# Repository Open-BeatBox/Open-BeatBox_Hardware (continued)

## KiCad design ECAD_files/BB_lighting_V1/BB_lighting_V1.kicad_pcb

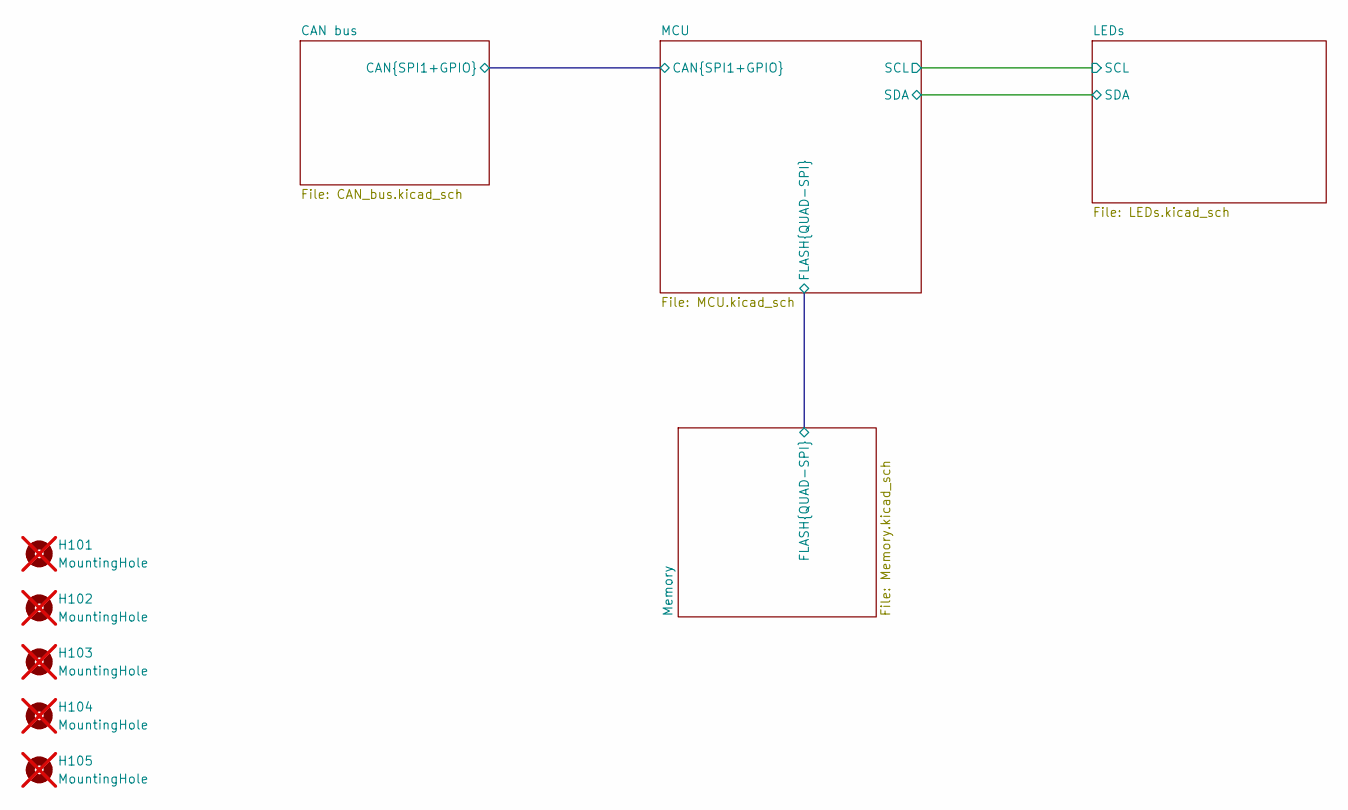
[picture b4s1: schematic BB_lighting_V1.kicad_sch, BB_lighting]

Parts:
H101, H102, H103, H104, H105: MountingHole; not fitted

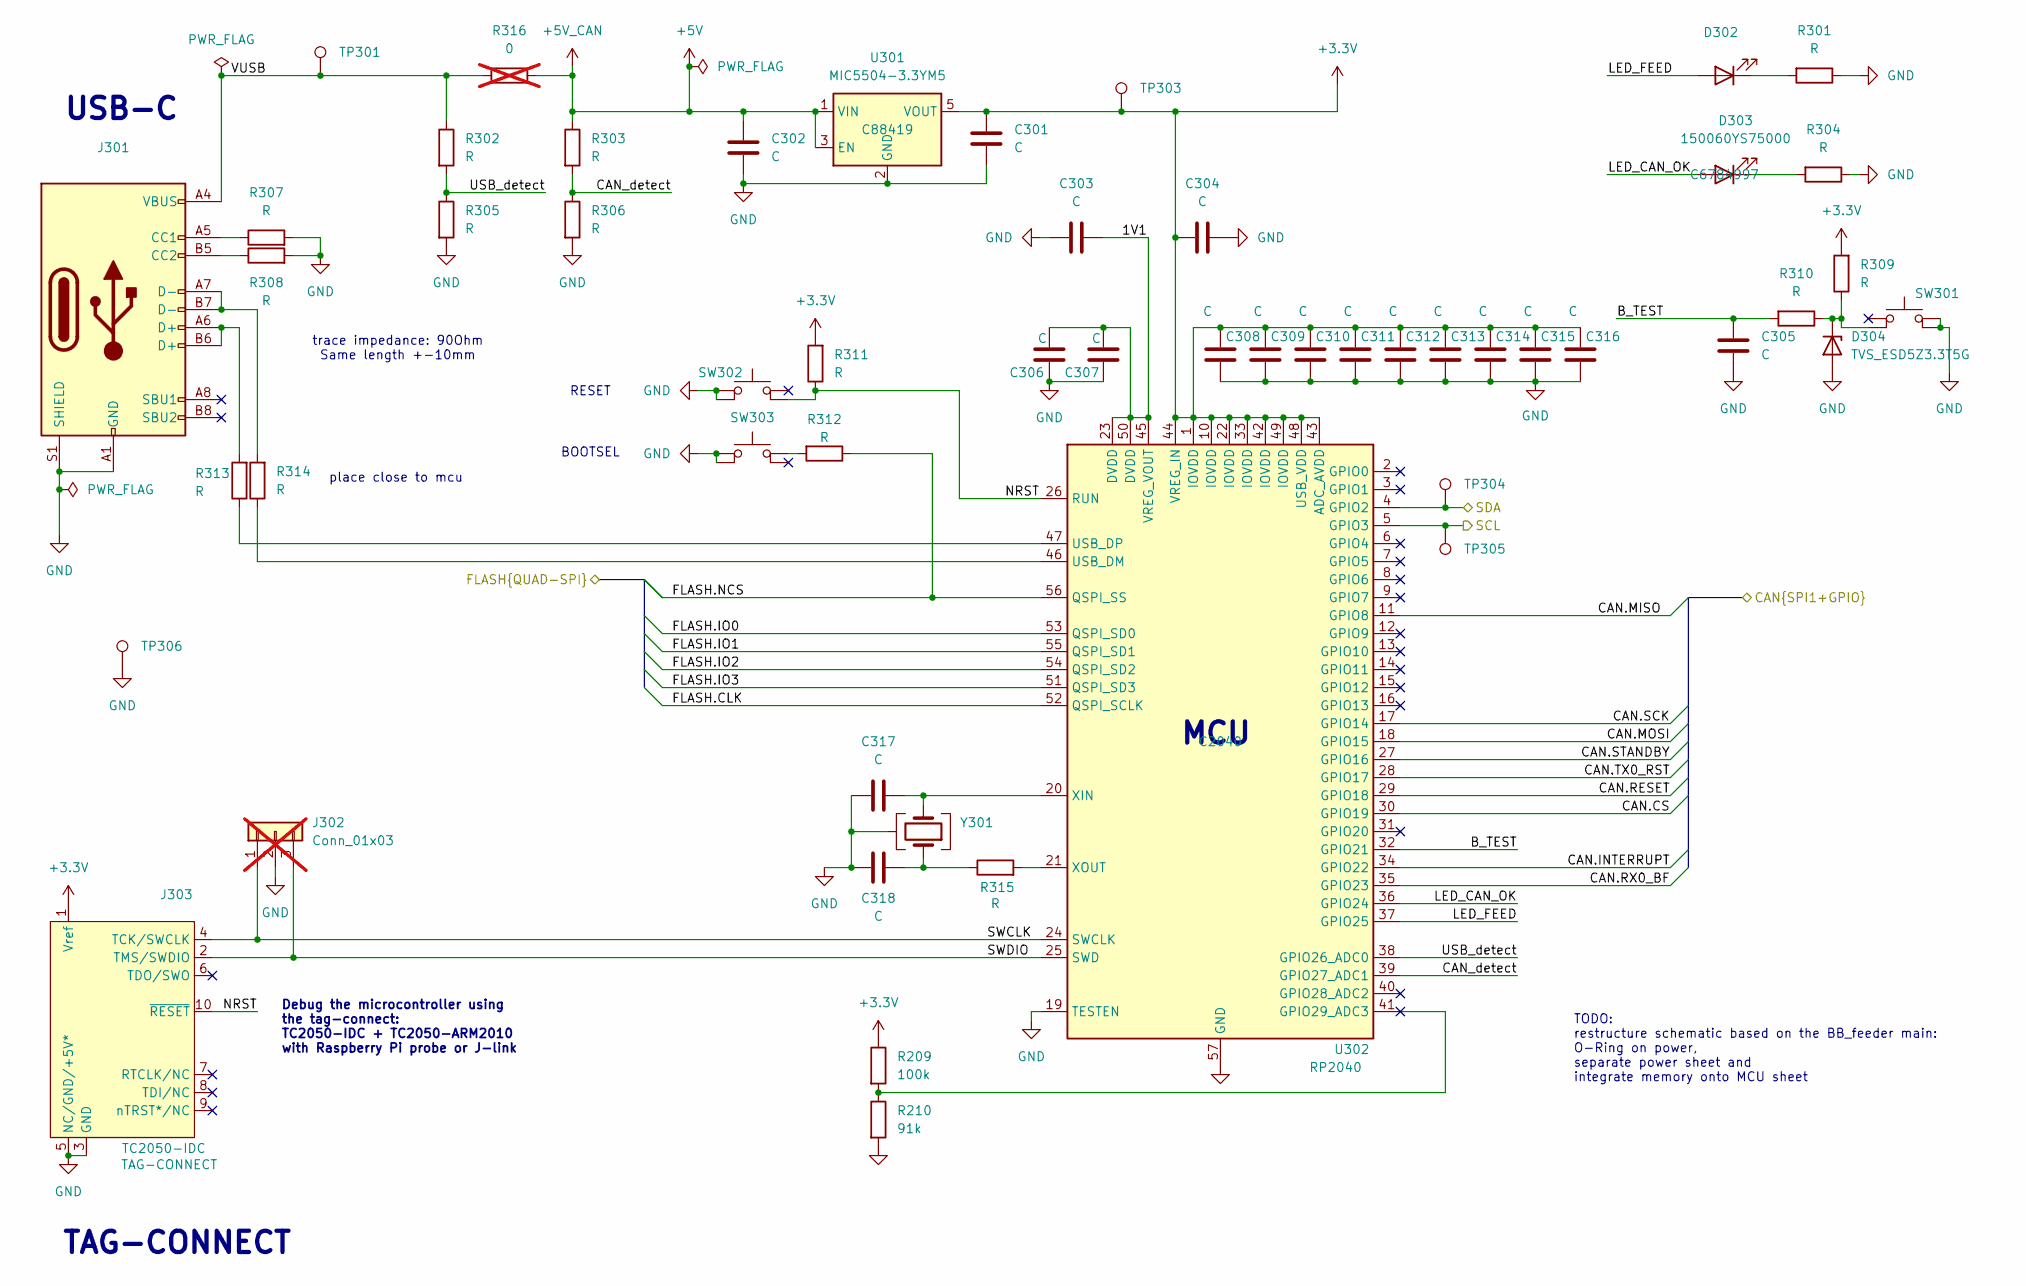
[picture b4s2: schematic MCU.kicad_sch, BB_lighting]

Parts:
C301, C302, C303, C304, C305, C306, C307, C308, C309, C310, C311, C312, C313, C314, C315, C316, C317, C318: C
D302: LED_150060GS75000; LED_0603_1608Metric; MPN 150060GS75000; JLCPCB Part C5252984
D303: LED_150060YS75000; LED_0603_1608Metric; MPN 150060YS75000; JLCPCB Part C6784997
D304: TVS_ESD5Z3.3T5G; D_SOD-523; MPN ESD5Z3.3T5G; JLCPCB Part C22440024
J301: Conn_USB-C_USB4105-GF-A; Conn_USB_C_Receptacle_GCT_USB4105-xx-A_16P_TopMnt_Horizontal; MPN USB4105-GF-A; JLCPCB Part C393939
J302: Conn_01x03; not fitted
J303: Conn_TagConnect_TC2050-IDC; Tag-Connect_TC2050-IDC-FP_2x05_P1.27mm_Vertical; MPN TC2050-IDC
R209: 100k; R_0603_1608Metric
R210: 91k; R_0603_1608Metric
R301, R302, R303, R304, R305, R306, R307, R308, R309, R310, R311, R312, R313, R314, R315: R
R316: 0; R_0603_1608Metric; not fitted
SW301, SW302, SW303: SW_TL3305AF160QG; SW_Push_TL3305; MPN TL3305AF160QG; JLCPCB Part C18078070
TP301, TP303, TP306: TestPoint; TestPoint_THTPad_D2.0mm_Drill1.0mm
TP304, TP305: TestPoint_SMD; TestPoint_Pad_D1.0mm
U301: MIC5504-3.3YM5; SOT-23-5; MPN MIC5504-3.3YM5; JLCPCB Part C88419
U302: RP2040; QFN-56-1EP_7x7mm_P0.4mm_EP3.2x3.2mm; MPN RP2040; JLCPCB Part C2040
Y301: Crystal_ABM8-272-T3; Crystal_SMD_Abracon_ABM8; MPN ABM8-272-T3; JLCPCB Part C20625731

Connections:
+3.3V: C301.1, C304.1, C308.1, C309.1, C310.1, C311.1, C312.1, C313.1, C314.1, C315.1, C316.1, J303.1 (Vref), R209.1, R309.2, R311.2, TP303.1 (1_1), U301.5 (VOUT), U302.1 (IOVDD), U302.10 (IOVDD), U302.22 (IOVDD), U302.33 (IOVDD), U302.42 (IOVDD), U302.43 (ADC_AVDD), U302.44 (VREG_IN), U302.48 (USB_VDD), U302.49 (IOVDD); also elsewhere on the board
+5V: C302.1, R303.1, R316.2, U301.1 (VIN), U301.3 (EN); also elsewhere on the board
/CAN bus/CAN.CS: U302.30 (GPIO19); also elsewhere on the board
/CAN bus/CAN.INTERRUPT: U302.34 (GPIO22); also elsewhere on the board
/CAN bus/CAN.MISO: U302.11 (GPIO8); also elsewhere on the board
/CAN bus/CAN.MOSI: U302.18 (GPIO15); also elsewhere on the board
/CAN bus/CAN.RESET: U302.29 (GPIO18); also elsewhere on the board
/CAN bus/CAN.RX0_BF: U302.35 (GPIO23); also elsewhere on the board
/CAN bus/CAN.SCK: U302.17 (GPIO14); also elsewhere on the board
/CAN bus/CAN.STANDBY: U302.27 (GPIO16); also elsewhere on the board
/CAN bus/CAN.TX0_RST: U302.28 (GPIO17); also elsewhere on the board
/LEDs/SCL: TP305.1 (1_1), U302.5 (GPIO3); also elsewhere on the board
/LEDs/SDA: TP304.1 (1_1), U302.4 (GPIO2); also elsewhere on the board
/MCU/1V1: C303.2, C306.2, C307.1, U302.23 (DVDD), U302.45 (VREG_VOUT), U302.50 (DVDD)
/MCU/B_TEST: C305.1, R310.2, U302.32 (GPIO21)
/MCU/CAN_detect: R303.2, R306.1, U302.39 (GPIO27_ADC1)
/MCU/FLASH.CLK: U302.52 (QSPI_SCLK); also elsewhere on the board
/MCU/FLASH.IO0: U302.53 (QSPI_SD0); also elsewhere on the board
/MCU/FLASH.IO1: U302.55 (QSPI_SD1); also elsewhere on the board
/MCU/FLASH.IO2: U302.54 (QSPI_SD2); also elsewhere on the board
/MCU/FLASH.IO3: U302.51 (QSPI_SD3); also elsewhere on the board
/MCU/FLASH.NCS: R312.1, U302.56 (QSPI_SS); also elsewhere on the board
/MCU/LED_CAN_OK: D303.2 (A), U302.36 (GPIO24)
/MCU/LED_FEED: D302.2 (A), U302.37 (GPIO25)
/MCU/NRST: J303.10 (~RESET), R311.1, SW302.2, U302.26 (RUN)
/MCU/SWCLK: J302.1, J303.4 (TCK/SWCLK), U302.24 (SWCLK)
/MCU/SWDIO: J302.3, J303.2 (TMS/SWDIO), U302.25 (SWD)
/MCU/USB_detect: R302.2, R305.1, U302.38 (GPIO26_ADC0)
/MCU/VUSB: J301.A4 (VBUS), J301.A9 (VBUS), J301.B4 (VBUS), J301.B9 (VBUS), R302.1, R316.1, TP301.1 (1_1)
GND: C301.2, C302.2, C303.1, C304.2, C305.2, C306.1, C307.2, C308.2, C309.2, C310.2, C311.2, C312.2, C313.2, C314.2, C315.2, C316.2, C317.1, C318.1, D304.2 (A), J301.A1 (GND), J301.A12 (GND), J301.B1 (GND), J301.B12 (GND), J301.S1 (SHIELD), J302.2, J303.3 (GND), J303.5 (NC/GND/+5V*), R210.2, R301.1, R304.1, R305.2, R306.2, R307.2, R308.2, SW301.1, SW301.2, SW302.3, SW302.4, SW303.1, SW303.2, TP306.1 (1_1), U301.2 (GND), U302.19 (TESTEN), U302.57 (GND), Y301.2, Y301.4; also elsewhere on the board
unnamed: C318.2, R315.1, Y301.1
unnamed: D302.1 (K), R301.2
unnamed: D303.1 (K), R304.2
unnamed: D304.1 (K), R309.1, R310.1, SW301.4
unnamed: J301.A5 (CC1), R307.1
unnamed: J301.B5 (CC2), R308.1
unnamed: J301.A6 (D+), J301.B6 (D+), R313.2
unnamed: J301.A7 (D-), J301.B7 (D-), R314.2
unnamed: R312.2, SW303.3
unnamed: R314.1, U302.46 (USB_DM)
unnamed: R313.1, U302.47 (USB_DP)
unnamed: C317.2, U302.20 (XIN), Y301.3
unnamed: R315.2, U302.21 (XOUT)

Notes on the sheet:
trace impedance: 90Ohm Same length +-10mm
TODO: restructure schematic based on the BB_feeder main: O-Ring on power, separate power sheet and integrate memory onto MCU sheet
TAG-CONNECT
MCU
place close to mcu
BOOTSEL
Debug the microcontroller using the tag-connect: TC2050-IDC + TC2050-ARM2010 with Raspberry Pi probe or J-link
RESET
USB-C

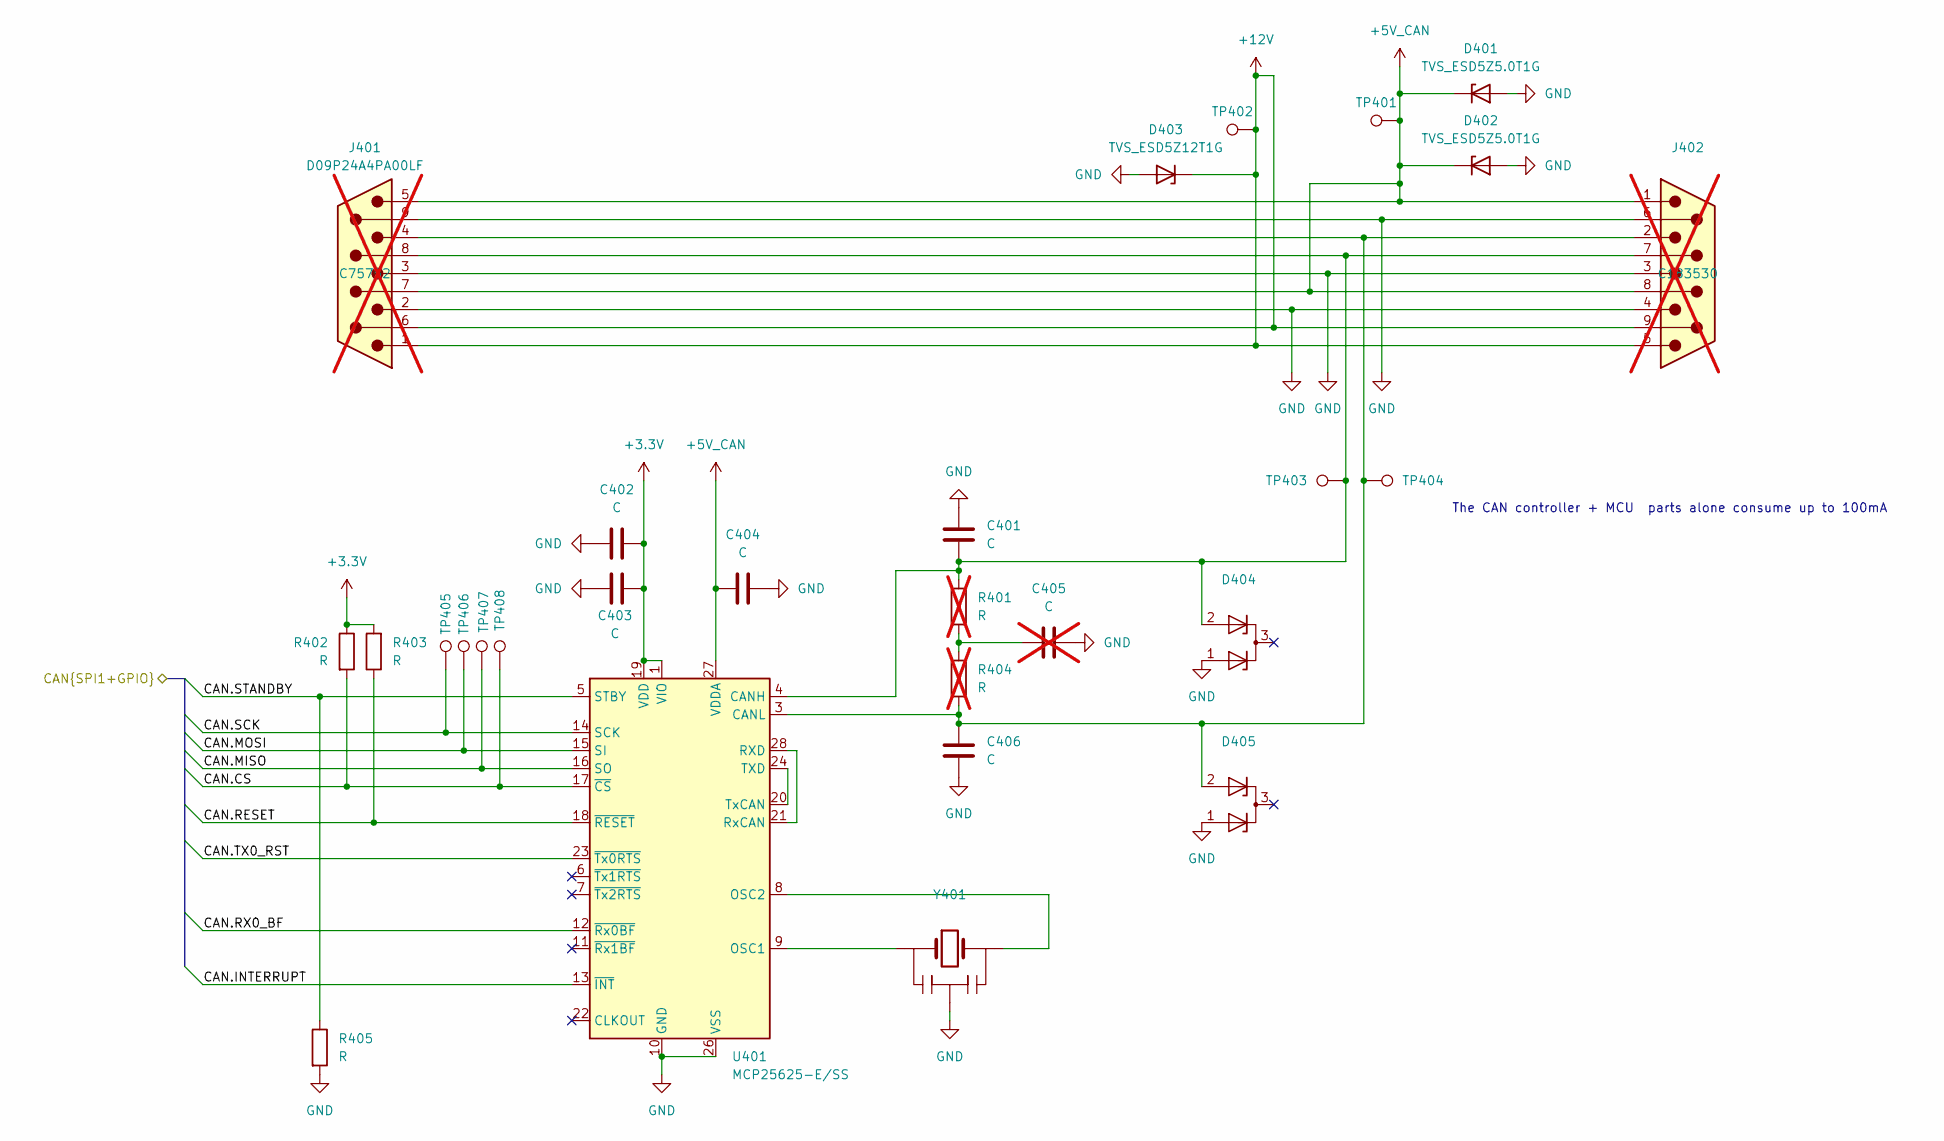
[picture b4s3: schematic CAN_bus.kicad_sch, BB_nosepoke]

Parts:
C401, C402, C403, C404, C406: C
C405: C; not fitted
D401, D402: TVS_ESD5Z5.0T1G; D_SOD-523; MPN ESD5Z5.0T1G; JLCPCB Part C343989
D403: TVS_ESD5Z12T1G; D_SOD-523; MPN ESD5Z12T1G
D404, D405: MMBZ27VCLT1G; SOT-23; MPN MMBZ27VCLT1G; JLCPCB Part C128609
J401: Conn-DB9_D09P24A4PA00LF; Conn_DB9_D09P24A4PA00LF; MPN D09P24A4PA00LF; JLCPCB Part C75752; not fitted
J402: Conn-DB9_D09S24A4PA00LF; Conn_DB9_D09S24A4PA00LF; MPN D09S24A4PA00LF; JLCPCB Part C183530; not fitted
R401, R404: R; not fitted
R402, R403, R405: R
TP401, TP402: TestPoint; TestPoint_THTPad_D2.0mm_Drill1.0mm
TP403, TP404, TP405, TP406, TP407, TP408: TestPoint_SMD; TestPoint_Pad_D1.0mm
U401: MCP25625-E/SS; SSOP-28_5.3x10.2mm_P0.65mm; MPN MCP25625-E/SS; JLCPCB Part C184944
Y401: CSTNE16M0VH3L000R0; Resonator_SMD_Murata_CSTxExxV-3Pin_3.0x1.1mm; MPN CSTNE16M0VH3L000R0; JLCPCB Part C1870467

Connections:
+3.3V: C402.2, C403.2, R402.1, R403.2, U401.1 (VIO), U401.19 (VDD); also elsewhere on the board
+5V: C404.1, D401.1 (K), D402.1 (K), J401.5, J401.7, J402.1, J402.8, TP401.1 (1_1), U401.27 (VDDA); also elsewhere on the board
+12V: D403.1 (K), J401.1, J401.6, J402.5, J402.9, TP402.1 (1_1); also elsewhere on the board
/CAN bus/CAN.CS: R402.2, TP408.1 (1_1), U401.17 (~CS); also elsewhere on the board
/CAN bus/CAN.INTERRUPT: U401.13 (~INT); also elsewhere on the board
/CAN bus/CAN.MISO: TP407.1 (1_1), U401.16 (SO); also elsewhere on the board
/CAN bus/CAN.MOSI: TP406.1 (1_1), U401.15 (SI); also elsewhere on the board
/CAN bus/CAN.RESET: R403.1, U401.18 (~RESET); also elsewhere on the board
/CAN bus/CAN.RX0_BF: U401.12 (~Rx0BF); also elsewhere on the board
/CAN bus/CAN.SCK: TP405.1 (1_1), U401.14 (SCK); also elsewhere on the board
/CAN bus/CAN.STANDBY: R405.1, U401.5 (STBY); also elsewhere on the board
/CAN bus/CAN.TX0_RST: U401.23 (~Tx0RTS); also elsewhere on the board
GND: C401.1, C402.1, C403.1, C404.2, C405.2, C406.2, D401.2 (A), D402.2 (A), D403.2 (A), D404.1 (K), D405.1 (K), J401.2, J401.3, J401.9, J402.3, J402.4, J402.6, R405.2, U401.10 (GND), U401.26 (VSS), Y401.2 (GND); also elsewhere on the board
unnamed: C405.1, R401.1, R404.2
unnamed: C401.2, D404.2 (K), J401.8, J402.7, R401.2, TP403.1 (1_1), U401.4 (CANH)
unnamed: C406.1, D405.2 (K), J401.4, J402.2, R404.1, TP404.1 (1_1), U401.3 (CANL)
unnamed: U401.9 (OSC1), Y401.1 (Input)
unnamed: U401.8 (OSC2), Y401.3 (Output)
unnamed: U401.21 (RxCAN), U401.28 (RXD)
unnamed: U401.20 (TxCAN), U401.24 (TXD)

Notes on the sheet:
The CAN controller + MCU parts alone consume up to 100mA

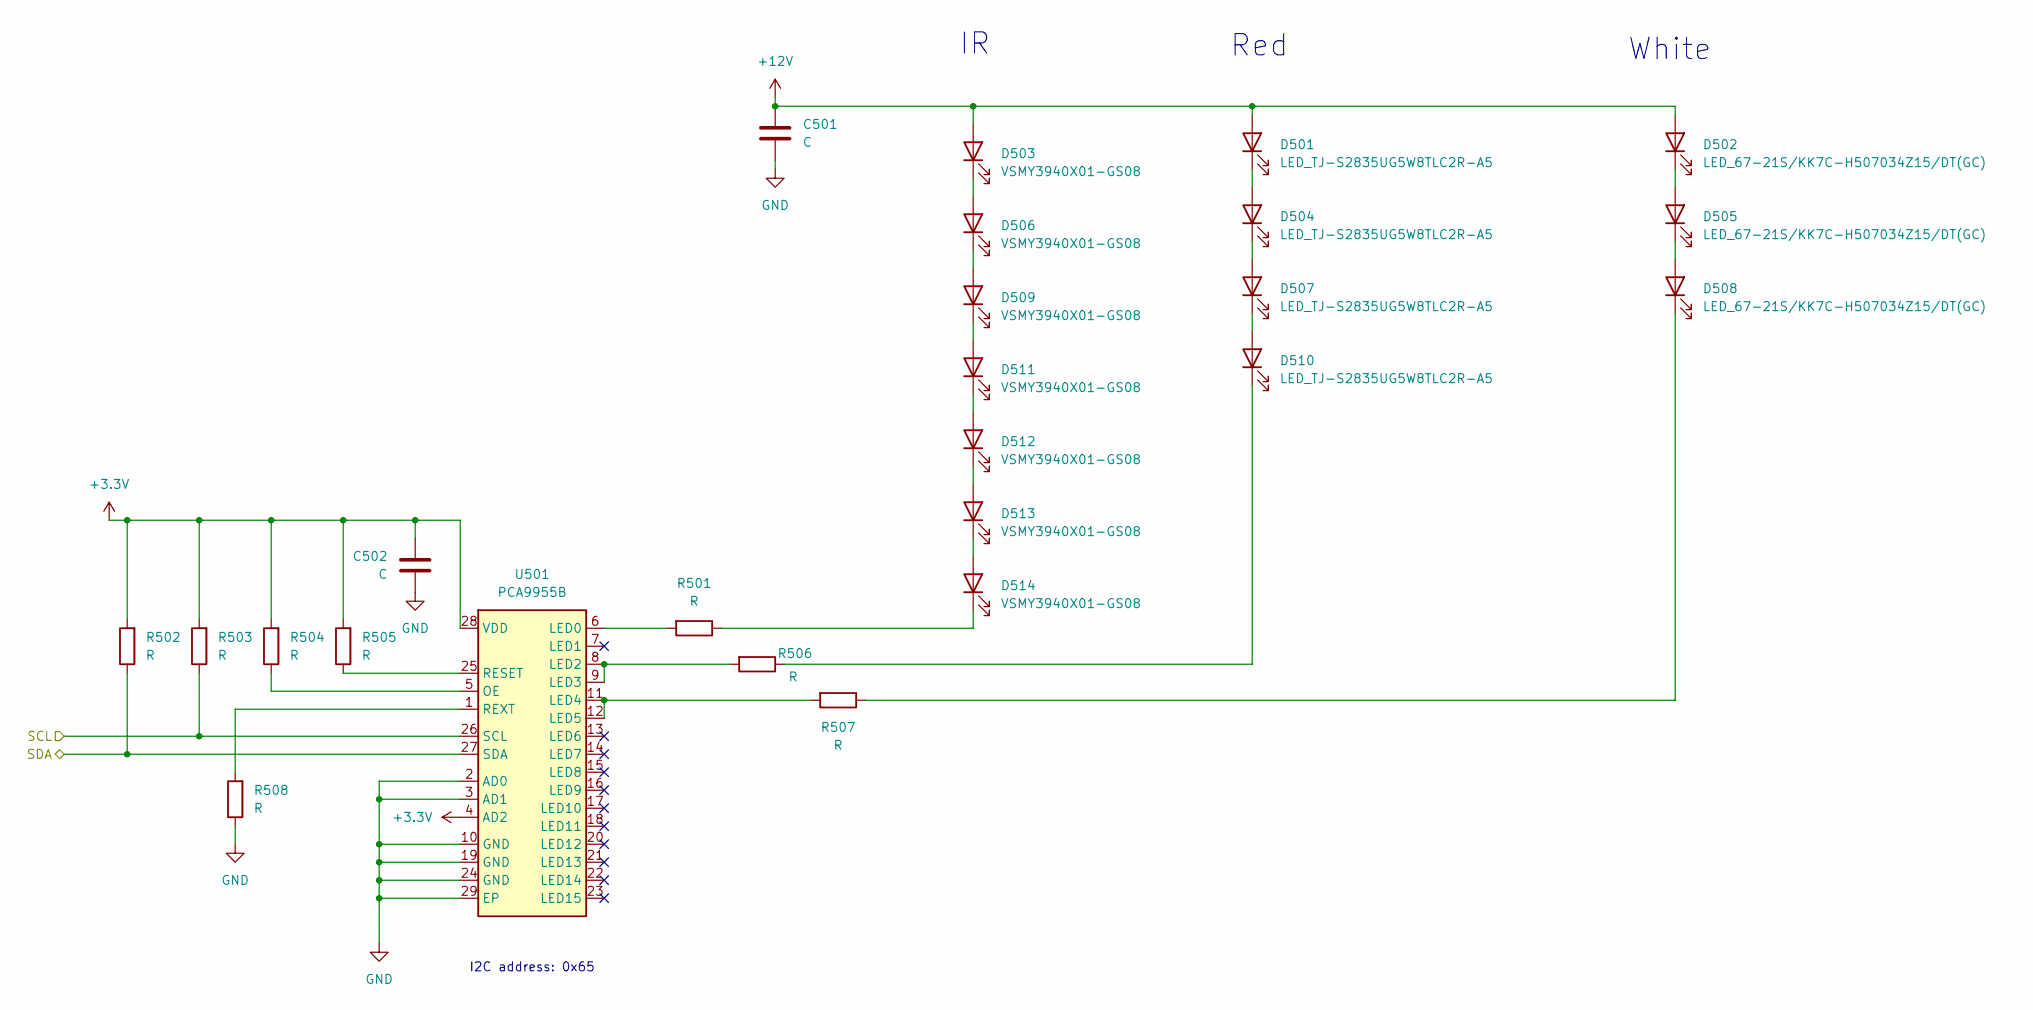
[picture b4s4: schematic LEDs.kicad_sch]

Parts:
C501, C502: C
D501, D504, D507, D510: LED_TJ-S2835UG5W8TLC2R-A5; LED_PLCC_2835_TOGIALED; MPN TJ-S2835UG5W8TLC2R-A5; JLCPCB Part C440450
D502, D505, D508: LED_67-21S/KK7C-H507034Z15/DT(GC); LED_PLCC_2835_Everlight; MPN 67-21S/KK7C-H507034Z15/DT(GC); JLCPCB Part C475394
D503, D506, D509, D511, D512, D513, D514: VSMY3940X01-GS08; LED_Vishay_PLCC-2; MPN VSMY3940X01-GS08; JLCPCB Part C962573
R501, R502, R503, R504, R505, R506, R507, R508: R
U501: PCA9955B; NXP_HTSSOP-28-1EP_4.4x9.7mm_P0.65mm_EP2.2x3.4mm; MPN PCA9955BTW/Q900J; JLCPCB Part C2678554

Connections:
+3.3V: C502.1, R502.2, R503.2, R504.2, R505.2, U501.4 (AD2), U501.28 (VDD); also elsewhere on the board
+12V: C501.1, D501.2 (A), D502.2 (A), D503.2 (A); also elsewhere on the board
/LEDs/SCL: R503.1, U501.26 (SCL); also elsewhere on the board
/LEDs/SDA: R502.1, U501.27 (SDA); also elsewhere on the board
GND: C501.2, C502.2, R508.1, U501.2 (AD0), U501.3 (AD1), U501.10 (GND), U501.19 (GND), U501.24 (GND), U501.29 (EP); also elsewhere on the board
unnamed: D501.1 (K), D504.2 (A)
unnamed: D502.1 (K), D505.2 (A)
unnamed: D503.1 (K), D506.2 (A)
unnamed: D504.1 (K), D507.2 (A)
unnamed: D505.1 (K), D508.2 (A)
unnamed: D506.1 (K), D509.2 (A)
unnamed: D507.1 (K), D510.2 (A)
unnamed: D508.1 (K), R507.1
unnamed: D509.1 (K), D511.2 (A)
unnamed: D510.1 (K), R506.1
unnamed: D511.1 (K), D512.2 (A)
unnamed: D512.1 (K), D513.2 (A)
unnamed: D513.1 (K), D514.2 (A)
unnamed: D514.1 (K), R501.1
unnamed: R501.2, U501.6 (LED0)
unnamed: R506.2, U501.8 (LED2), U501.9 (LED3)
unnamed: R507.2, U501.11 (LED4), U501.12 (LED5)
unnamed: R504.1, U501.5 (OE)
unnamed: R505.1, U501.25 (RESET)
unnamed: R508.2, U501.1 (REXT)

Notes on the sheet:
Red
I2C address: 0x65
White

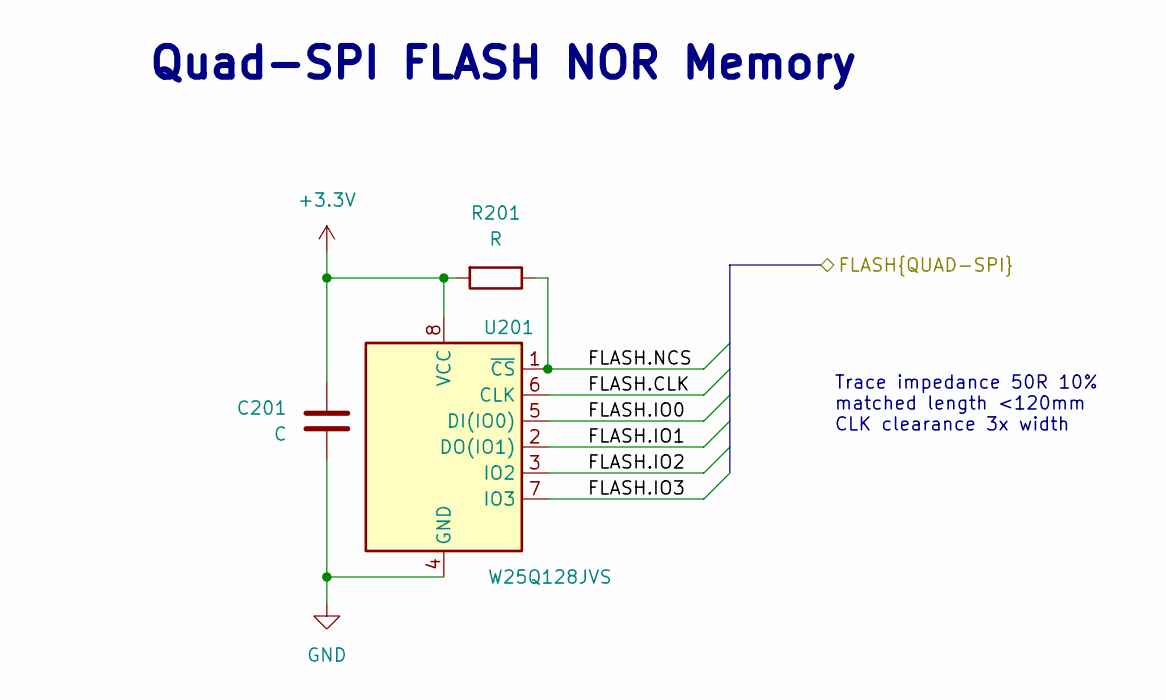
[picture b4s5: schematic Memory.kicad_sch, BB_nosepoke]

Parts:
C201: C
R201: R
U201: W25Q128JVS; SOIC-8_W25Q128JV; MPN W25Q128JVS; JLCPCB Part C97521

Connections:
+3.3V: C201.2, R201.2, U201.8 (VCC); also elsewhere on the board
/MCU/FLASH.CLK: U201.6 (CLK); also elsewhere on the board
/MCU/FLASH.IO0: U201.5 (DI(IO0)); also elsewhere on the board
/MCU/FLASH.IO1: U201.2 (DO(IO1)); also elsewhere on the board
/MCU/FLASH.IO2: U201.3 (IO2); also elsewhere on the board
/MCU/FLASH.IO3: U201.7 (IO3); also elsewhere on the board
/MCU/FLASH.NCS: R201.1, U201.1 (~CS); also elsewhere on the board
GND: C201.1, U201.4 (GND); also elsewhere on the board

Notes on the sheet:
Trace impedance 50R 10% matched length <120mm CLK clearance 3x width
Quad-SPI FLASH NOR Memory

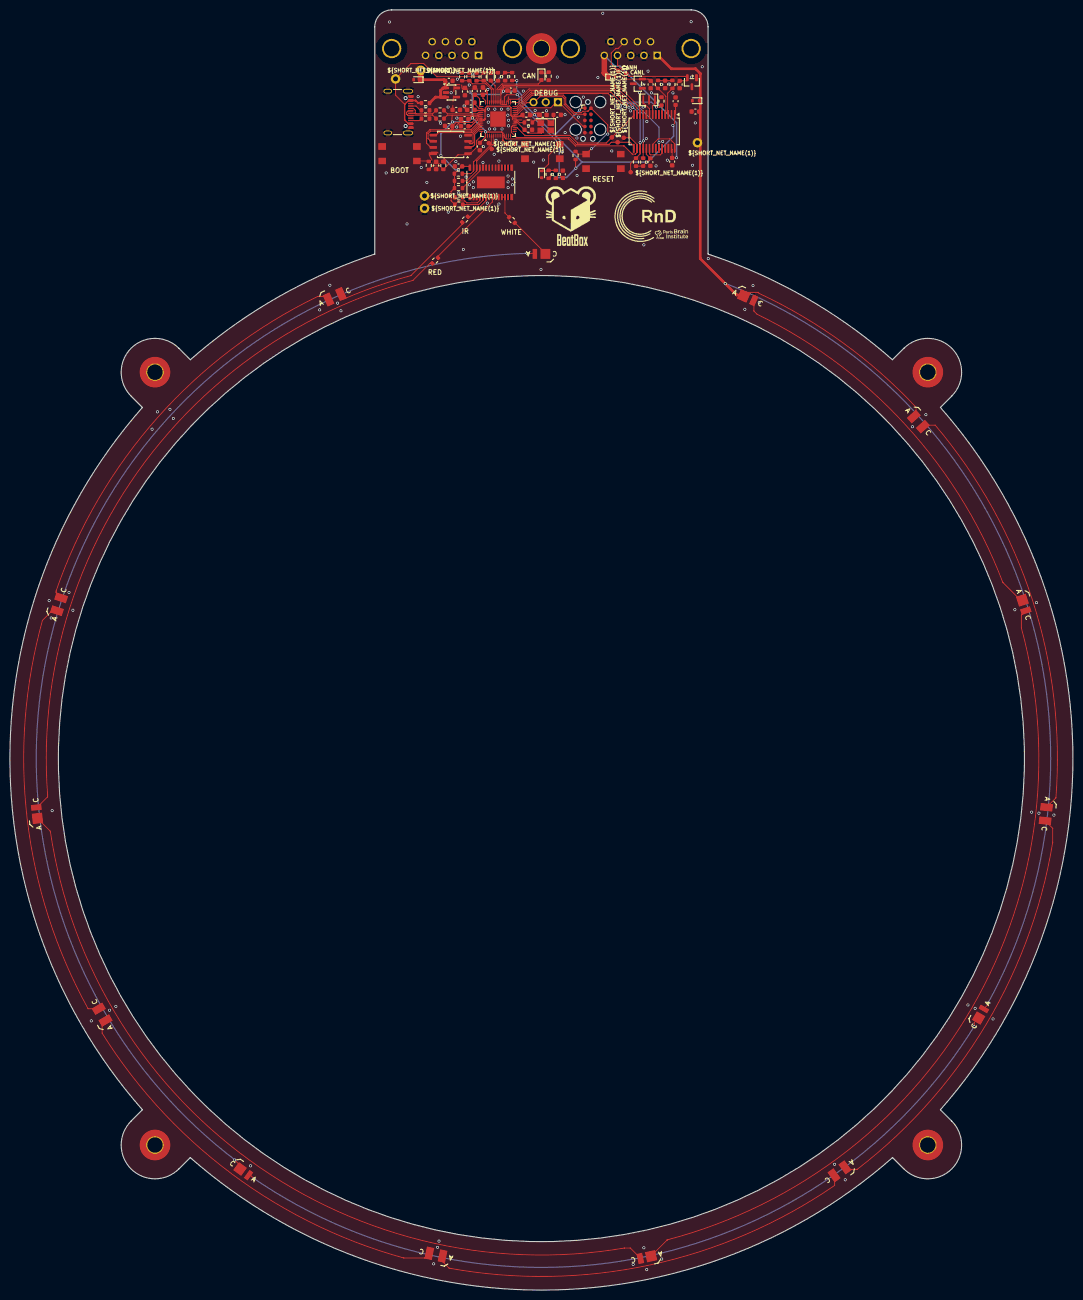
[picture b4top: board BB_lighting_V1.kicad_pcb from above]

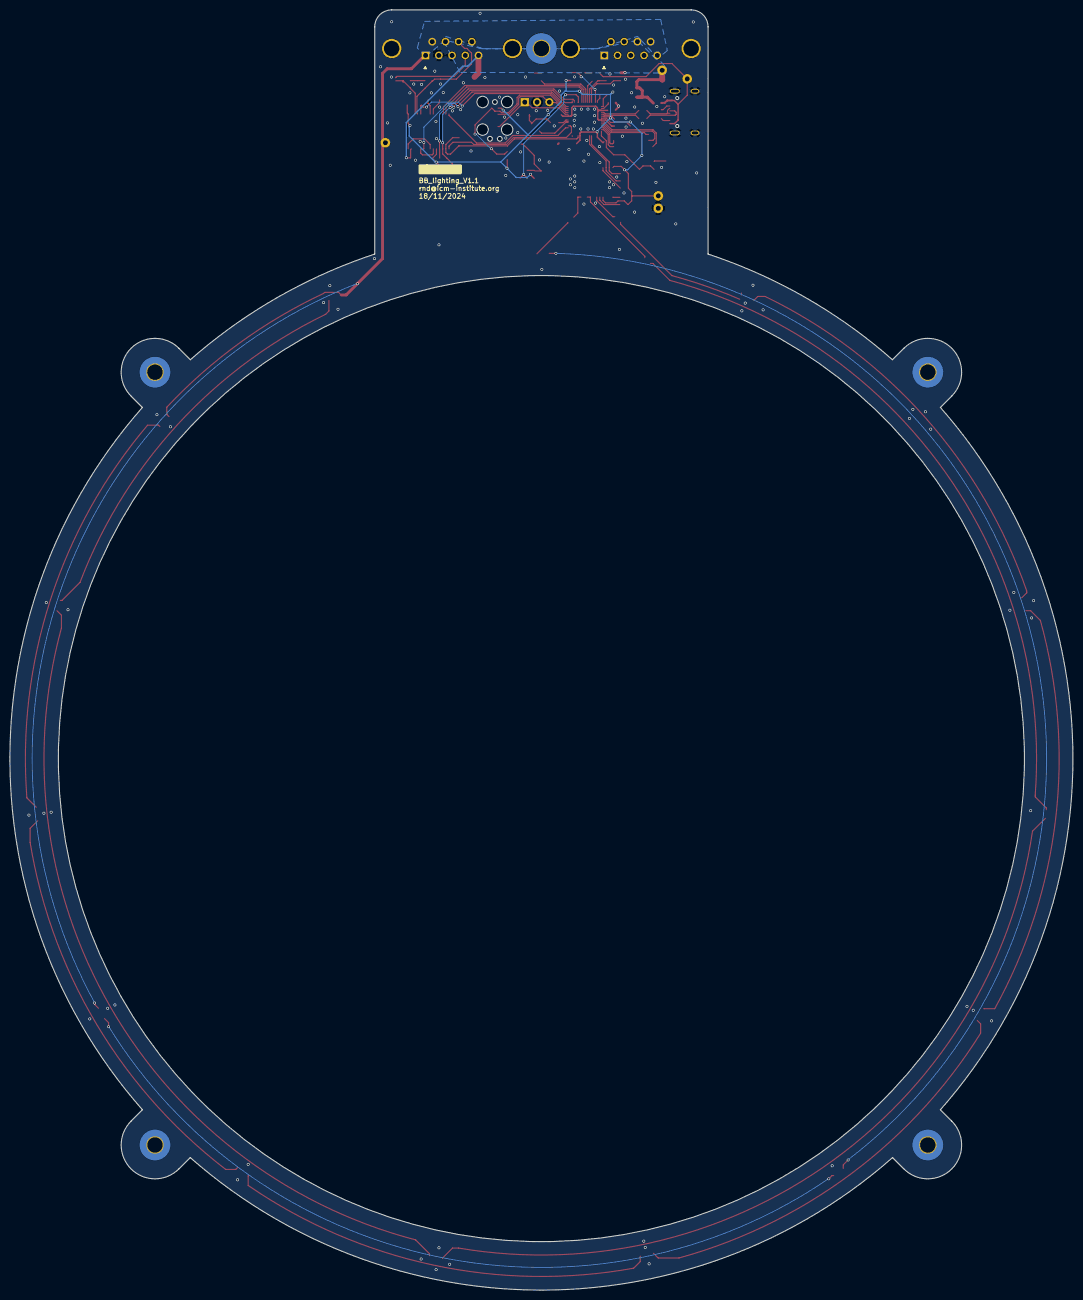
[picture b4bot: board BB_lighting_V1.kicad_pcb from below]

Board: 4 copper layers, 220.1 x 265.0 mm, 115 parts (2 on the bottom side), 71 nets.

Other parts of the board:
G2: LOGO

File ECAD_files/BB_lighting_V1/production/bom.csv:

Designator,Footprint,Quantity,Value,LCSC Part #
"C201, C301, C302, C303, C304, C305, C306, C307, C308, C309, C310, C311, C312, C313, C314, C315, C316, C317, C318, C401, C402, C403, C404, C406, C501, C502",0603,26,C,
D301,SOT-23,1,D_SDM40E20LC,C155330
D302,0603,1,LED_150060GS75000,C5252984
D303,0603,1,LED_150060YS75000,C6784997
D304,D_SOD-523,1,TVS_ESD5Z3.3T5G,C22440024
"D401, D402",D_SOD-523,2,TVS_ESD5Z5.0T1G,C343989
D403,D_SOD-523,1,TVS_ESD5Z12T1G,ESD5Z12T1G
"D404, D405",SOT-23,2,MMBZ27VCLT1G,C128609
"D501, D504, D507, D510",LED_PLCC_2835_TOGIALED,4,LED_TJ-S2835UG5W8TLC2R-A5,C440450
"D502, D505, D508",LED_PLCC_2835_Everlight,3,LED_67-21S/KK7C-H507034Z15/DT(GC),C475394
"D503, D506, D509, D511, D512, D513, D514",LED_Vishay_PLCC-2,7,VSMY3940X01-GS08,C962573
J301,Conn_USB_C_Receptacle_GCT_USB4105-xx-A_16P_TopMnt_Horizontal,1,Conn_USB-C_USB4105-GF-A,C393939
"R201, R301, R302, R303, R304, R305, R306, R307, R308, R309, R310, R311, R312, R313, R314, R315, R402, R403, R405, R501, R502, R503, R504, R505, R506, R507, R508",0603,27,R,
"SW301, SW302, SW303",SW_Push_TL3305,3,SW_TL3305AF160QG,C18078070
U201,SOIC-8_W25Q128JV,1,W25Q128JVS,C97521 
U301,SOT-23-5,1,MIC5504-3.3YM5,C88419
U302,QFN-56-1EP_7x7mm_P0.4mm_EP3.2x3.2mm,1,RP2040,C2040
U401,SSOP-28_5.3x10.2mm_P0.65mm,1,MCP25625-E/SS,C184944
U501,NXP_HTSSOP-28-1EP_4.4x9.7mm_P0.65mm_EP2.2x3.4mm,1,PCA9955B,C2678554
Y301,Crystal_SMD_Abracon_ABM8,1,Crystal_ABM8-272-T3,C20625731
Y401,Resonator_SMD_Murata_CSTxExxV-3Pin_3.0x1.1mm,1,CSTNE16M0VH3L000R0,C1870467

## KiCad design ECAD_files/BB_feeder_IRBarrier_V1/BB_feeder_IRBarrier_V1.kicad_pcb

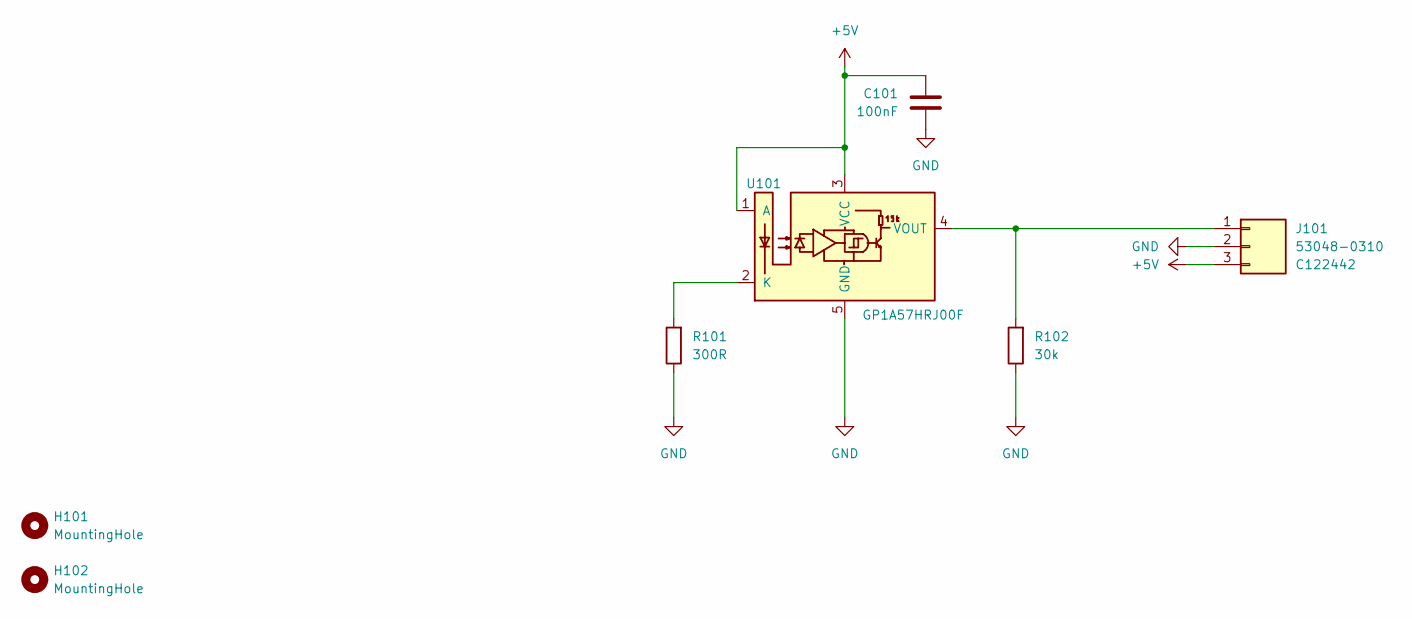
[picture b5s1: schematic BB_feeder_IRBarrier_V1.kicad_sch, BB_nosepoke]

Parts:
C101: 100nF; C_0603_1608Metric
H101, H102: MountingHole; MountingHole_3.2mm_M3_Pad_TopBottom
J101: Conn_Picoblade_Molex_53047-0310; Conn_Molex_PicoBlade_53048-0310_1x03_P1.25mm_Horizontal; MPN 53048-0310; JLC Part C122442
R101: 300R; R_0603_1608Metric
R102: 30k; R_0603_1608Metric
U101: GP1A57HRJ00F; SHARP-GP1A57HRJ00F; MPN GP1A57HRJ00F; JLC Part C919627

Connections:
+5V: C101.2, J101.3, U101.1 (A), U101.3 (VCC)
GND: C101.1, J101.2, R101.1, R102.1, U101.5 (GND)
unnamed: J101.1, R102.2, U101.4 (VOUT)
unnamed: R101.2, U101.2 (K)

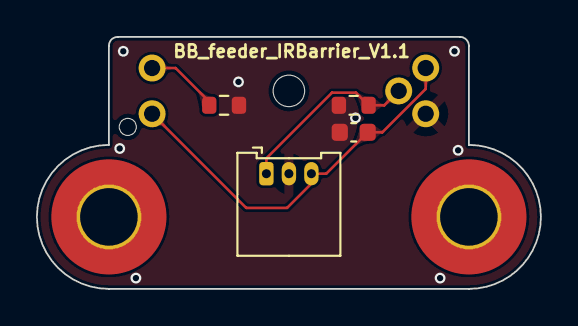
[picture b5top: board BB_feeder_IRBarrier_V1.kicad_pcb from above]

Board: 4 copper layers, 28.0 x 14.0 mm, 7 parts (1 on the bottom side), 4 nets.

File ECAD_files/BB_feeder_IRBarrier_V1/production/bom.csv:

Designator,Footprint,Quantity,Value,LCSC Part #
C101,0603,1,100nF,
J101,Conn_Molex_PicoBlade_53048-0310_1x03_P1.25mm_Horizontal,1,53048-0310,C122442
R101,0603,1,300R,
R102,0603,1,30k,
U101,SHARP-GP1A57HRJ00F,1,GP1A57HRJ00F,C919627

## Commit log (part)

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2025-08-01 Initial project structure
2025-08-01 Initial dev branch commit
2025-08-01 Initial dev_electronics branch commit
2025-08-01 Initial dev_mechanics branch commit
2026-02-04 UPDATE: add design parts and production parts
